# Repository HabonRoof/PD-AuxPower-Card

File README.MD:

# Type-C PD Auxiliary power supply
### _Light, small, isolated digial power_
Tiny-Aux is a small protable auxiliary digital power supply for electrical engineer using everyday.
As a power electronic engineer, I'm tired moving heavy linear bench power for only less then 1W power.
So I develop this Tiny-Aux for four different voltage as auxiliary power source.
It sould support USB type-C connector and PD protocol fand four different output voltage, but now can only draw 5V input.
Most importantly, it's isolated from primary and secondary, ground path is no more concerned.
## Appearence

The two ER9.5 transformer provide physical isolation side by side.
There are two output channel provide 3.3V/5V and 12V/24V saperately. Use two switches to set the output voltage of each channel.
The black/yellow wire and ground pin is for debugging.
## Features
- PWM limit protection
- UART real-time power monitoring

## Fearures to be develop
- Over current/ Over voltage protection
- FUSB302B driver library
- EEPROM for power event recording

## Specification
- Input voltage: 5V-24V (USB PD is in development)
- Channel 1 output voltage: 3.3V/ 5V
- Channel 1 output current: 1000 mA
- Channel 2 output voltage: 12V/ 24V
- Channel 2 output current: 500 mA
- Total putput wattage: 2W

## Technical detail
All of the component can be placed or soldered by machine automatically, **but no transformer**.
This project using flyback topology as isolated power, so the transformer is the key component and need to satisfy following charactisic.
The bobbin size used is ER9.5, core material is PC44, diameter of conductor is 0.5 mm.
The transformer need grind air-gap manualy. The distant is about 0.5mm. (Need to be confirm).
For **Channel 1** 3.3V/5V rail, the transformer should have this charactisic:
- Primary inductance: 330uH, roughtly 10 turns
- Secondary inductance: 30uH, roughtly 30 turns
 -Leakage inductance: 10uH

For **Channel 2** 12V/24V rail, the transformer should have this charactisic:
- Primary inductance: 30uH, roughtly 3 turns
- Secondary inductance: 330uH, roughtly 30 turns
- Leakage inductance: 10uH

The **dot point** of transformer is marked on PCB schematic file, **DOUBLE CHECK the polarity**.

The switching frequency is set to 200kHz, using voltage control for stable output voltage.
PID parameter can be tune to best for dynamic load.

## Important Notice
The communication pin (UART, Debug interface) is grounded with primary side of Tiny-Aux module, please DO NOT connect to the output channel incase burn your computer.
Over current protection and over voltage protection is not implement yet!
USB PD ptorocol is not implement yet!

## Known Issue
- PD protocol can not read PDO message.
- 5V transient will go into unstable state when applying 100 mA 1000mA dynamic load.
- TPS62177 EN pin connect to GND (fixed in schematic)

## Contribute
If you want to join the development, please feel free to send me e-mail, and I'll send you the hardware for free.

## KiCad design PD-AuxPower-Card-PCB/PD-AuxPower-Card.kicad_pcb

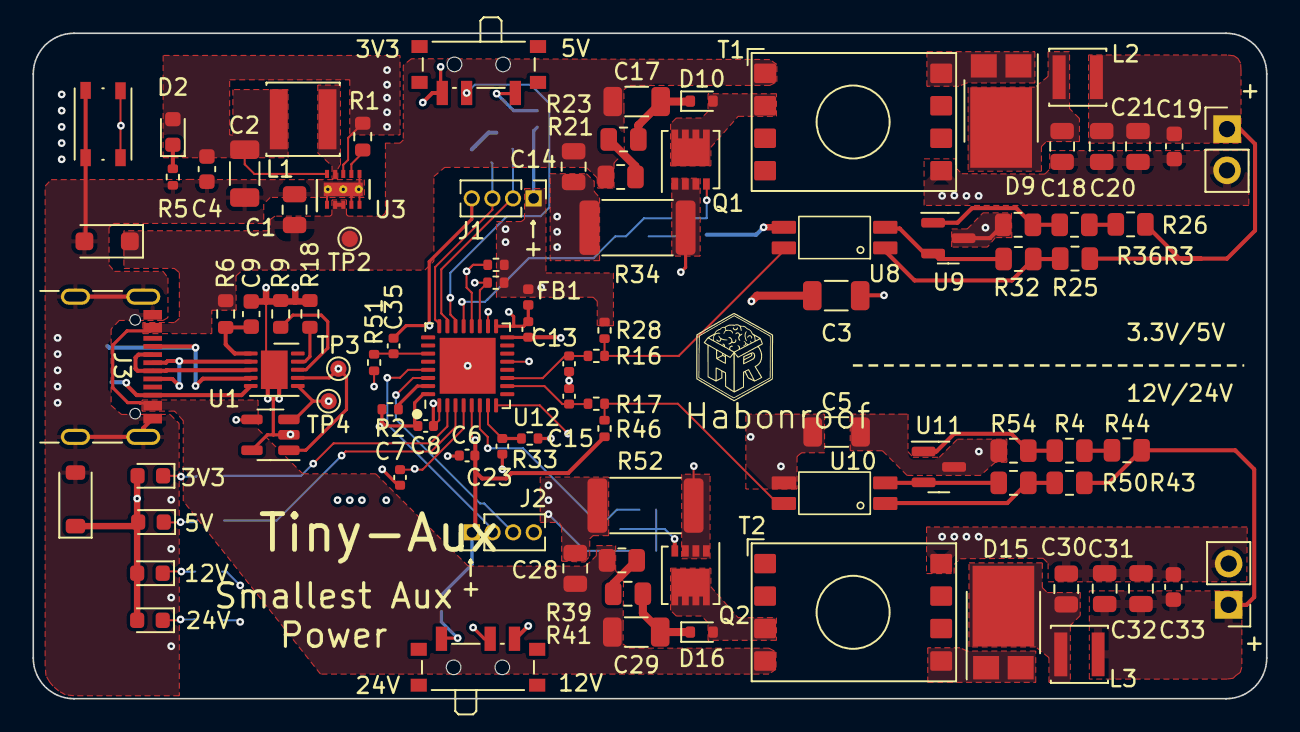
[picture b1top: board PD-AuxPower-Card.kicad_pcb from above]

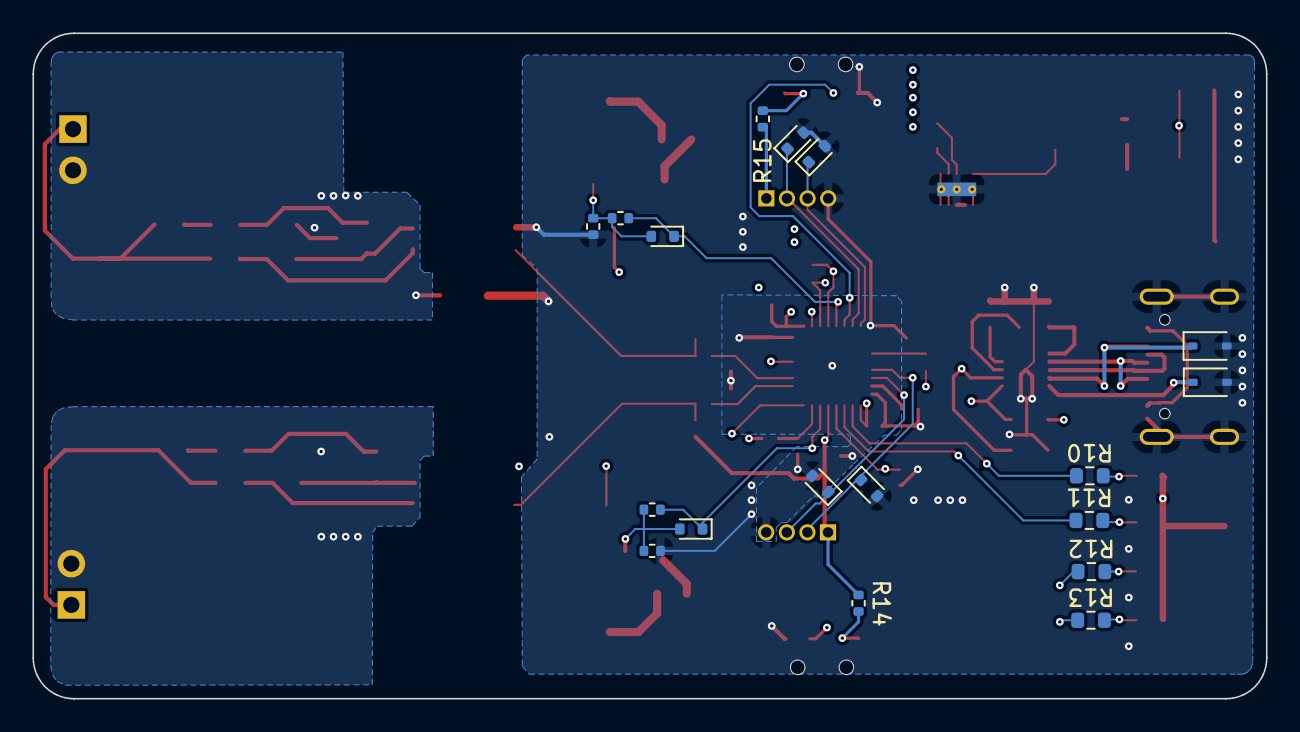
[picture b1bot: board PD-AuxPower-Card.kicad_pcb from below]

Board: 4 copper layers, 76.0 x 41.0 mm, 112 parts (18 on the bottom side), 68 nets.

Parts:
C1: 2.2u/35V; C_0805_2012Metric
C2: 22u/10V; C_1206_3216Metric
C3, C5: 2200p/500V; C_1206_3216Metric
C4, C19, C33: 0.1u; C_0603_1608Metric
C6, C7, C8, C10: 0.1u; C_0402_1005Metric
C9: 1u; C_0603_1608Metric
C13, C15: 100n; C_0402_1005Metric
C14, C18, C20, C21, C28, C30, C31, C32: 10u/50V; C_0805_2012Metric
C17, C29: 222/100V; C_1206_3216Metric
C23, C35: 47p; C_0402_1005Metric
D1, D11, D13, D17: MM5Z3V3; D_SOD-523
D2, D5, D6, D7, D8: LED; D_0603_1608Metric
D3: SMF3.3A; D_SOD-123
D4: SMF28A; D_SOD-123F
D9, D15: PMEG045V100EPE; Nexperia_CFP15_SOT-1289
D10, D12, D16, D18: 1N4148; D_SOD-523
D19, D21: CDSOD323-T05LC; D_SOD-323
FB1: 220Ω@100MHz; L_0402_1005Metric
J1: SWD; PinHeader_1x04_P1.27mm_Vertical
J2: UART; PinHeader_1x04_P1.27mm_Vertical
J3: USB_C_Receptacle_USB2.0; USB_C_Receptacle_GCT_USB4105-xx-A_16P_TopMnt_Horizontal
J4, J5: 2.54mm terminal; PinHeader_1x02_P2.54mm_Vertical
L1: 10uH; L_Changjiang_FNR4010S
L2, L3: 2.2u; L_Changjiang_FNR3012S
Q1, Q2: FDMC86520L; Diodes_PowerDI3333-8
R1: 100k; R_0603_1608Metric
R2, R5, R14, R15, R30, R48: 10k; R_0402_1005Metric
R3: 8.2k; R_0805_2012Metric
R4, R26: 0; R_0805_2012Metric
R6: 10; R_0603_1608Metric
R7, R8: 4.7k; R_0402_1005Metric
R9, R10, R11, R12, R13, R18: 10k; R_0603_1608Metric
R16, R17, R33, R51: 1k; R_0402_1005Metric
R21, R23, R39, R41: 100; R_0805_2012Metric
R24, R42: 10; R_0402_1005Metric
R25: 1k; R_0805_2012Metric
R28, R46: 50; R_0402_1005Metric
R32, R50: NC; R_0805_2012Metric
R34, R52: 1; R_2512_6332Metric
R36, R54: 10k; R_0805_2012Metric
R43: 6.8k; R_0805_2012Metric
R44: 33k; R_0805_2012Metric
SW1: TSA017A2510A; SW_Push_1P1T_NO_Vertical_Wuerth_434133025816
SW2, SW3: K3-1296S-E1; SW_SPDT_PCM12
T1, T2: ER 9.5; Transformer_ER9.5_11.6mmx8.2mm
TP2: VIN; TestPoint_Pad_D1.0mm
TP3: SCL; TestPoint_Pad_D1.0mm
TP4: SDA; TestPoint_Pad_D1.0mm
U1: HUSB328_DD2; DFN-10-1EP_3x3mm_P0.5mm_EP1.65x2.38mm
U3: TPS62177DQC; WSON-10-1EP_2x3mm_P0.5mm_EP0.84x2.4mm_ThermalVias
U4: K24C02; SOT-23-5
U8, U10: LTV-217; SOP-4-175mil
U9: TLV431BFTA; SOT-23
U11: TL431DBZ; SOT-23
U12: STM32L432KCUx; QFN-32-1EP_5x5mm_P0.5mm_EP3.45x3.45mm

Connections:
+3V3: C2.1, C4.1, C6.1, D2.2 (A), D3.1 (A1), D5.2 (A), D6.2 (A), D7.2 (A), D8.2 (A), FB1.2, J1.1, J2.1, L1.2, R1.2, R7.1, R8.1, R14.1, R15.1, R28.1, R46.1, U3.8 (~SLEEP), U3.10 (VOS), U4.4 (Vcc), U12.5 (VDDA)
BOOT0: R2.1, U12.31 (PH3)
DRV1: D12.1 (K), R24.2, U12.21 (PA11)
DRV2: D18.1 (K), R42.2, U12.6 (PA0)
GND: C1.2, C2.2, C3.1, C4.2, C5.1, C6.2, C7.2, C8.2, C9.2, C10.2, C13.2, C14.2, C15.2, C23.2, C28.2, C35.2, D1.2 (A), D3.2 (A2), D4.2 (A2), D11.2 (A), D13.2 (A), D17.2 (A), D19.2 (A2), D21.2 (A2), J1.4, J2.4, J3.A1 (GND), J3.A12 (GND), J3.B1 (GND), J3.B12 (GND), J3.S1 (SHIELD), R2.2, R5.2, R9.2, R18.2, R30.1, R34.2, R48.1, R52.2, SW1.1, SW2.3 (C), SW3.3 (C), U1.11 (GND), U3.1 (PGND), U3.4 (NC), U3.5 (FB), U3.6 (AGND), U3.11 (PAD), U4.2 (GND), U4.5 (WP), U8.3, U10.3, U12.16 (VSS), U12.32 (VSS), U12.33 (VSS)
GND1: C3.2, C18.2, C19.2, C20.2, C21.2, J4.2, R36.1, T1.5 (AB), U9.3 (A)
GND2: C5.2, C30.2, C31.2, C32.2, C33.2, J5.2, R54.1, T2.8 (AA), U11.3 (A)
I2C1_SCL: R8.2, TP3.1, U1.7 (SCL), U4.1 (SCL), U12.19 (PA9)
I2C1_SDA: R7.2, TP4.1, U1.6 (SDA), U4.3 (SDA), U12.20 (PA10)
Iout1_fb: C23.1, R33.1, U12.7 (PA1)
Iout2_fb: C35.1, R51.1, U12.27 (PB4)
LED_3v3: R10.1, U12.2 (PC14)
LED_5v: R11.1, U12.3 (PC15)
LED_12v: R12.1, U12.13 (PA7)
LED_24v: R13.1, U12.8 (PA2)
NRST: C7.1, SW1.2, U12.4 (NRST)
unnamed: C8.1, C10.1, FB1.1, U12.1 (VDD), U12.17 (VDD)
unnamed: D2.1 (K), R5.1
unnamed: D5.1 (K), R10.2
unnamed: D6.1 (K), R11.2
unnamed: D7.1 (K), R12.2
unnamed: D8.1 (K), R13.2
unnamed: C18.1, D9.3 (K), L2.1
unnamed: D10.2 (A), Q1.5 (D), T1.2 (SB)
unnamed: C17.2, D10.1 (K), R23.1
unnamed: D12.2 (A), Q1.4 (G), R24.1, R30.2
unnamed: C30.1, D15.3 (K), L3.1
unnamed: D16.2 (A), Q2.5 (D), T2.3 (SC)
unnamed: C29.2, D16.1 (K), R41.1
unnamed: D18.2 (A), Q2.4 (G), R42.1, R48.2
unnamed: D19.1 (A1), J3.A5 (CC1), U1.4 (CC1)
unnamed: D21.1 (A1), J3.B5 (CC2), U1.5 (CC2)
unnamed: C19.1, C20.1, C21.1, J4.1, L2.2, R25.2, R26.2
unnamed: C31.1, C32.1, C33.1, J5.1, L3.2, R43.2, R44.2
unnamed: Q1.1 (S), R33.2, R34.1
unnamed: Q2.1 (S), R51.2, R52.1
unnamed: R4.2, R44.1
unnamed: R16.2, R28.2, U8.4
unnamed: R17.2, R46.2, U10.4
unnamed: R21.1, R23.2
unnamed: R25.1, R32.2, U8.1
unnamed: R3.2, R26.1
unnamed: R39.1, R41.2
unnamed: R43.1, R50.2, U10.1
unnamed: R14.2, SW2.1 (A)
unnamed: R15.2, SW3.1 (A)
unnamed: D9.1 (A), D9.2 (A), T1.8 (AA)
unnamed: D15.1 (A), D15.2 (A), T2.5 (AB)
unnamed: J3.A6 (D+), J3.B6 (D+), U1.2 (D+)
unnamed: J3.A7 (D-), J3.B7 (D-), U1.3 (D-)
unnamed: R18.1, U1.9 (ISET)
unnamed: C9.1, R6.2, U1.1 (VIN)
unnamed: R9.1, U1.8 (VSET)
unnamed: R1.1, U3.7 (PG)
unnamed: L1.1, U3.9 (SW)
unnamed: R32.1, U8.2, U9.2 (K)
unnamed: R3.1, R36.2, U9.1 (REF)
unnamed: R50.1, U10.2, U11.2 (K)
unnamed: R4.1, R54.2, U11.1 (REF)
SWCLK: D1.1 (K), J1.3, U12.24 (PA14)
SWDIO: D11.1 (K), J1.2, U12.23 (PA13)
UART_RX: D13.1 (K), J2.3, U12.30 (PB7)
UART_TX: D17.1 (K), J2.2, U12.29 (PB6)
VBUS: C1.1, C14.1, C17.1, C28.1, C29.1, D4.1 (A1), J3.A4 (VBUS), J3.A9 (VBUS), J3.B4 (VBUS), J3.B9 (VBUS), R6.1, R21.2, R39.2, T1.1 (SA), T2.4 (SD), TP2.1, U3.2 (VIN), U3.3 (EN)
Vout1_fb: C13.1, R16.1, U12.11 (PA5)
Vout1_sel: SW2.2 (B), U12.18 (PA8)
Vout2_fb: C15.1, R17.1, U12.10 (PA4)
Vout2_sel: SW3.2 (B), U12.22 (PA12)

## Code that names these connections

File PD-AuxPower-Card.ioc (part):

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Mcu.Name=STM32L432K(B-C)Ux
Mcu.Package=UFQFPN32
Mcu.UserName=STM32L432KCUx
PA0.GPIOParameters=GPIO_Label
PA0.GPIO_Label=DRV2
PA0.Signal=S_TIM2_CH1
PA1.Mode=INP
PA1.Signal=COMP1_INP
PA10.Mode=I2C
PA10.Signal=I2C1_SDA
PA11.GPIOParameters=GPIO_Label
PA11.GPIO_Label=DRV1
PA11.Signal=S_TIM1_CH4
PA12.GPIOParameters=GPIO_Label
PA12.GPIO_Label=Vout1_sel
PA12.Signal=GPIO_Input
PA13\ (JTMS-SWDIO).GPIOParameters=GPIO_Label
PA13\ (JTMS-SWDIO).GPIO_Label=SWDIO
PA13\ (JTMS-SWDIO).Mode=Serial_Wire
PA13\ (JTMS-SWDIO).Signal=SYS_JTMS-SWDIO
PA14\ (JTCK-SWCLK).GPIOParameters=GPIO_Label
PA14\ (JTCK-SWCLK).GPIO_Label=SWCLK
PA14\ (JTCK-SWCLK).Mode=Serial_Wire
PA14\ (JTCK-SWCLK).Signal=SYS_JTCK-SWCLK
PA2.GPIOParameters=PinState,GPIO_Label
PA2.GPIO_Label=LED_24v
PA2.PinState=GPIO_PIN_RESET
PA2.Signal=GPIO_Output
PA4.GPIOParameters=GPIO_PuPd,GPIO_Label,GPIO_Mode
PA4.GPIO_Label=Vout2_FB
PA4.GPIO_Mode=GPIO_MODE_ANALOG_ADC_CONTROL
PA4.GPIO_PuPd=GPIO_NOPULL
PA4.Signal=ADCx_IN9
PA5.GPIOParameters=GPIO_PuPd,GPIO_Label,GPIO_Mode
PA5.GPIO_Label=Vout1_FB
PA5.GPIO_Mode=GPIO_MODE_ANALOG_ADC_CONTROL
PA5.GPIO_PuPd=GPIO_NOPULL
PA5.Signal=ADCx_IN10
PA7.GPIOParameters=GPIO_Label
PA7.GPIO_Label=LED_12v
PA7.Signal=GPIO_Output
PA8.GPIOParameters=GPIO_Label
PA8.GPIO_Label=Vout2_sel
PA8.Signal=GPIO_Input
PA9.Mode=I2C
PA9.Signal=I2C1_SCL
PB4\ (NJTRST).Mode=INP
PB4\ (NJTRST).Signal=COMP2_INP
PB6.Mode=Asynchronous
PB6.Signal=USART1_TX
PB7.Mode=Asynchronous
PB7.Signal=USART1_RX
PC14-OSC32_IN\ (PC14).GPIOParameters=GPIO_PuPd,GPIO_Label,GPIO_ModeDefaultOutputPP
PC14-OSC32_IN\ (PC14).GPIO_Label=LED_3v3
PC14-OSC32_IN\ (PC14).GPIO_ModeDefaultOutputPP=GPIO_MODE_OUTPUT_PP
PC14-OSC32_IN\ (PC14).GPIO_PuPd=GPIO_NOPULL
PC14-OSC32_IN\ (PC14).Signal=GPIO_Output
PC15-OSC32_OUT\ (PC15).GPIOParameters=GPIO_Label,GPIO_ModeDefaultOutputPP
PC15-OSC32_OUT\ (PC15).GPIO_Label=LED_5v
PC15-OSC32_OUT\ (PC15).GPIO_ModeDefaultOutputPP=GPIO_MODE_OUTPUT_PP
PC15-OSC32_OUT\ (PC15).Signal=GPIO_Output
RCC.HSE_VALUE=8000000
RCC.SYSCLKFreq_VALUE=80000000
RCC.SYSCLKSource=RCC_SYSCLKSOURCE_PLLCLK
board=NUCLEO-L432KC
boardIOC=true

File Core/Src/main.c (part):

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/* Private user code ---------------------------------------------------------*/
/* USER CODE BEGIN 0 */
uint16_t ADC_res[2] = {0};
uint16_t Iout1_FB = 0;
uint16_t Iout2_FB = 0;
uint16_t Vout1_FB = 0;
uint16_t Vout2_FB = 0;
uint32_t timer15_ctr = 0;
uint32_t timer16_ctr = 0;
uint16_t adc_isr_ctr = 0;
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  __HAL_RCC_GPIOB_CLK_ENABLE();

  /*Configure GPIO pin Output Level */
  HAL_GPIO_WritePin(GPIOC, LED_3v3_Pin|LED_5v_Pin, GPIO_PIN_RESET);

  /*Configure GPIO pin Output Level */
  HAL_GPIO_WritePin(GPIOA, LED_24v_Pin|LED_12v_Pin, GPIO_PIN_RESET);

  /*Configure GPIO pins : LED_3v3_Pin LED_5v_Pin */
  GPIO_InitStruct.Pin = LED_3v3_Pin|LED_5v_Pin;
  GPIO_InitStruct.Mode = GPIO_MODE_OUTPUT_PP;
  GPIO_InitStruct.Pull = GPIO_NOPULL;
  GPIO_InitStruct.Speed = GPIO_SPEED_FREQ_LOW;
  HAL_GPIO_Init(GPIOC, &GPIO_InitStruct);

  /*Configure GPIO pins : LED_24v_Pin LED_12v_Pin */
  GPIO_InitStruct.Pin = LED_24v_Pin|LED_12v_Pin;
  GPIO_InitStruct.Mode = GPIO_MODE_OUTPUT_PP;
  GPIO_InitStruct.Pull = GPIO_NOPULL;
  GPIO_InitStruct.Speed = GPIO_SPEED_FREQ_LOW;
  HAL_GPIO_Init(GPIOA, &GPIO_InitStruct);

  /*Configure GPIO pins : Vout2_sel_Pin Vout1_sel_Pin */
  GPIO_InitStruct.Pin = Vout2_sel_Pin|Vout1_sel_Pin;
  GPIO_InitStruct.Mode = GPIO_MODE_INPUT;
  GPIO_InitStruct.Pull = GPIO_NOPULL;
  HAL_GPIO_Init(GPIOA, &GPIO_InitStruct);
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	// 65kHz update rate
	adc_isr_ctr = 0;
	// Read The ADC Conversion result to variables
	Vout2_FB = ADC_res[0];	// PA4
	Vout1_FB = ADC_res[1];	// PA5

	Vout1_pid_param.adc_fb_value = Vout1_FB;
	pid_process(&Vout1_pid_param);
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
void HAL_TIM_PeriodElapsedCallback(TIM_HandleTypeDef *htim){
	if(htim == &htim16){
		SW_3v3_5v  = HAL_GPIO_ReadPin(Vout1_sel_GPIO_Port, Vout1_sel_Pin);
		SW_12v_24v = HAL_GPIO_ReadPin(Vout2_sel_GPIO_Port, Vout2_sel_Pin);

		if(SW_3v3_5v != SW_3v3_5v_old){
			SW_3v3_5v_old = SW_3v3_5v;
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
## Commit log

2023-07-13 ADD: First commit for PD auxiliary power project.
2023-07-22 Initial commit. Add source file of PCB and Firmware, the firmware not support any communication yet, but only can show LED effect for its alive.
2023-07-29 FEAT: Add house keeping timer (tim16 )for checking switches status. Add I2C test function asking FUSB302B some data.
2023-08-03 FEAT: Add ADC sampling function for current/voltage sensing. Using timer16 ISR to trigger ADC DMA sampling request, and put the value into different variable for controller used.
2023-08-03 FEAT: Add UART communication showing 4 ADC read value and output voltage mode select status. baud rate = 115200, no parity bit, stop bit is set to 1.
2023-08-03 FEAT: Add PWM feature for MOSFET driven
2023-08-11 FEAT: Change PWM frequency to 50kHz, fix LED indicator bug PCB FIX: Adjust ophotocoupler feedback resistor value
2023-08-11 update datasheet
2023-08-12 FEAT: Add PID algorithm for output voltage control. NOT TUNE YET! Change ADC1 trigger source into TIM1 TRGO for update event. Synchronised TIM2 and TIM1 by using slave mode. PCB: Change TL431 to TLV4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
2023-08-13 PCB: Update LTV-214 footprint and update to PCB layout.
2023-08-24 FEAT: Increase PWM frequency to 200kHz, add PD protocol lib prototype. PCB: Add comment of 12/24V feedback loop. Doc: Change technical reference manual for STM32L4xx
2023-09-29 FEAT: Set I2C mode to standard mode(100kHz), change FUSB302B driver header file definition, trimming output voltage of 3.3/5V channel and 12/24V channel by optocoupler current reduce to 1mA. Add rese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
2023-09-29 FEAT: Add CC pin detect feature for CC communication switch setup.
2023-10-01 FEAT: Add FUSB302B_read_all function to storage FUSB302B register data into data structure to monitor the chip.
2023-10-01 FEAT: Disable PD logic reset
2023-10-10 FEAT: Add readme document
2023-12-07 FEAT: Revolution PCB to ver 1.0. Change COMP1+ to 3v3 current sense, COMP2+ to 12V current sense and 12V LED to GPIO7 output. Modify PCB layout.
2023-12-28 HW: FEAT: Relayout circuit and some adjustment. FW: Change .ico file to match schematic, add COMP for current limiting
2024-02-14 FEAT: Add Matlab file (Octave capable) for calculation transformer parameter. Modify PCB schematic Redefine pinout, ISR and peripherial

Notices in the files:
Core/Src/main.c:
Copyright (c) 2023 STMicroelectronics.
All rights reserved.
This software is licensed under terms that can be found in the LICENSE file
